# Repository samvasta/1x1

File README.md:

# 1x1
Repository for a modular 1x1 keyswitch PCB

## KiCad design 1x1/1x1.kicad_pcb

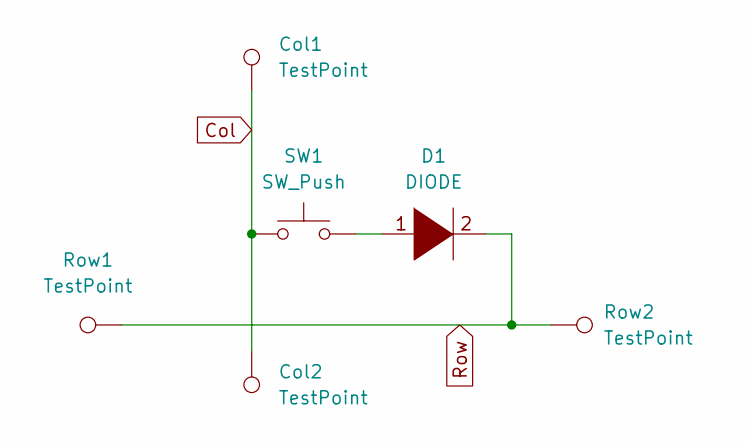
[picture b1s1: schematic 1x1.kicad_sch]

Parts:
Col1, Col2: TestPoint; SinglePad
D1: DIODE; D_MiniMELF_Handsoldering
Row1, Row2: TestPoint; SinglePad
SW1: SW_Push; Kailh_socket_reversible

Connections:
Col: Col1.1, Col2.1, SW1.1
unnamed 1: D1.1 (K), SW1.2; also elsewhere on the board
Row: D1.2 (A), Row1.1, Row2.1; also elsewhere on the board

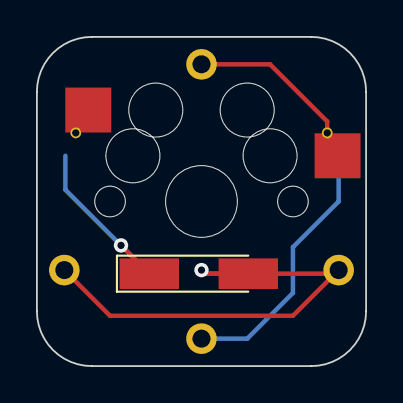
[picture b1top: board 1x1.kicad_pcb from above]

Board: 2 copper layers, 18.3 x 18.3 mm, 7 parts (1 on the bottom side), 3 nets.

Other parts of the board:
D1#2: DIODE; D_MiniMELF_Handsoldering

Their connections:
unnamed 1: D1#2.1 (K); also elsewhere on the board
Row: D1#2.2 (A); also elsewhere on the board

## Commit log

2024-02-19 Impl 1x1 hotswap pcb
